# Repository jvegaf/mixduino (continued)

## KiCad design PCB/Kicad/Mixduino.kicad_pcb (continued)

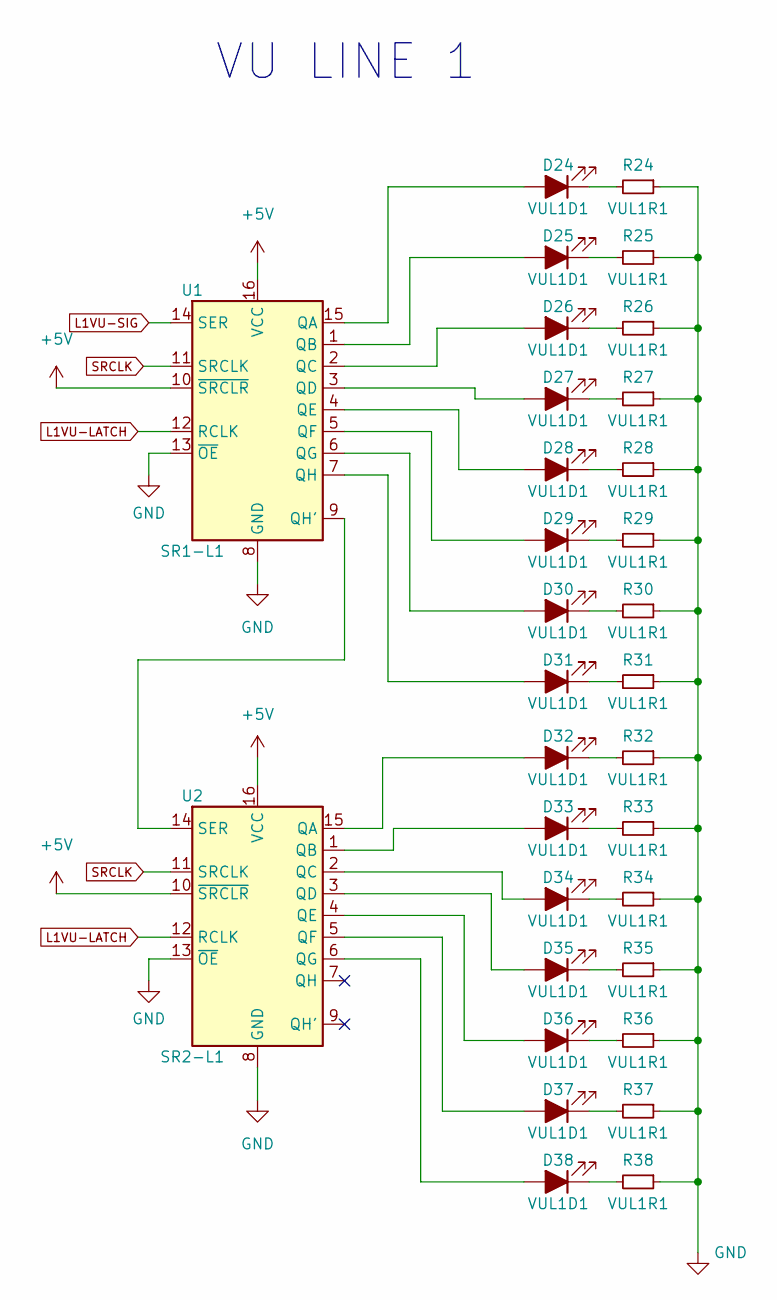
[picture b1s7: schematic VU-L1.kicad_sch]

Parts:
D24, D25, D26, D27, D28, D29, D30, D31, D32: VUL1D1; LED_GREEN
D33, D34, D35, D36: VUL1D1; LED_YELLOW
D37, D38: VUL1D1; LED_RED
R24, R25, R26, R27, R28, R29, R30, R31, R32, R33, R34, R35, R36, R37, R38: VUL1R1; R_1206_3216Metric_Pad1.30x1.75mm_HandSolder
U1: SR1-L1; SO-16_3.9x9.9mm_P1.27mm
U2: SR2-L1; SO-16_3.9x9.9mm_P1.27mm

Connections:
GND: R24.1, R25.1, R26.1, R27.1, R28.1, R29.1, R30.1, R31.1, R32.1, R33.1, R34.1, R35.1, R36.1, R37.1, R38.1, U1.8 (GND), U1.13 (~OE), U2.8 (GND), U2.13 (~OE); also elsewhere on the board
L1VU-LATCH: U1.12 (RCLK), U2.12 (RCLK); also elsewhere on the board
L1VU-SIG: U1.14 (SER); also elsewhere on the board
unnamed: D24.1 (K), R24.2
unnamed: D24.2 (A), U1.15 (QA)
unnamed: D25.1 (K), R25.2
unnamed: D25.2 (A), U1.1 (QB)
unnamed: D26.1 (K), R26.2
unnamed: D26.2 (A), U1.2 (QC)
unnamed: D27.1 (K), R27.2
unnamed: D27.2 (A), U1.3 (QD)
unnamed: D28.1 (K), R28.2
unnamed: D28.2 (A), U1.4 (QE)
unnamed: D29.1 (K), R29.2
unnamed: D29.2 (A), U1.5 (QF)
unnamed: D30.1 (K), R30.2
unnamed: D30.2 (A), U1.6 (QG)
unnamed: D31.1 (K), R31.2
unnamed: D31.2 (A), U1.7 (QH)
unnamed: D32.1 (K), R32.2
unnamed: D32.2 (A), U2.15 (QA)
unnamed: D33.1 (K), R33.2
unnamed: D33.2 (A), U2.1 (QB)
unnamed: D34.1 (K), R34.2
unnamed: D34.2 (A), U2.2 (QC)
unnamed: D35.1 (K), R35.2
unnamed: D35.2 (A), U2.3 (QD)
unnamed: D36.1 (K), R36.2
unnamed: D36.2 (A), U2.4 (QE)
unnamed: D37.1 (K), R37.2
unnamed: D37.2 (A), U2.5 (QF)
unnamed: D38.1 (K), R38.2
unnamed: D38.2 (A), U2.6 (QG)
unnamed: U1.9 (QH'), U2.14 (SER)
SRCLK: U1.11 (SRCLK), U2.11 (SRCLK); also elsewhere on the board
VCC: U1.10 (~SRCLR), U1.16 (VCC), U2.10 (~SRCLR), U2.16 (VCC); also elsewhere on the board

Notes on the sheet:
VU LINE 1

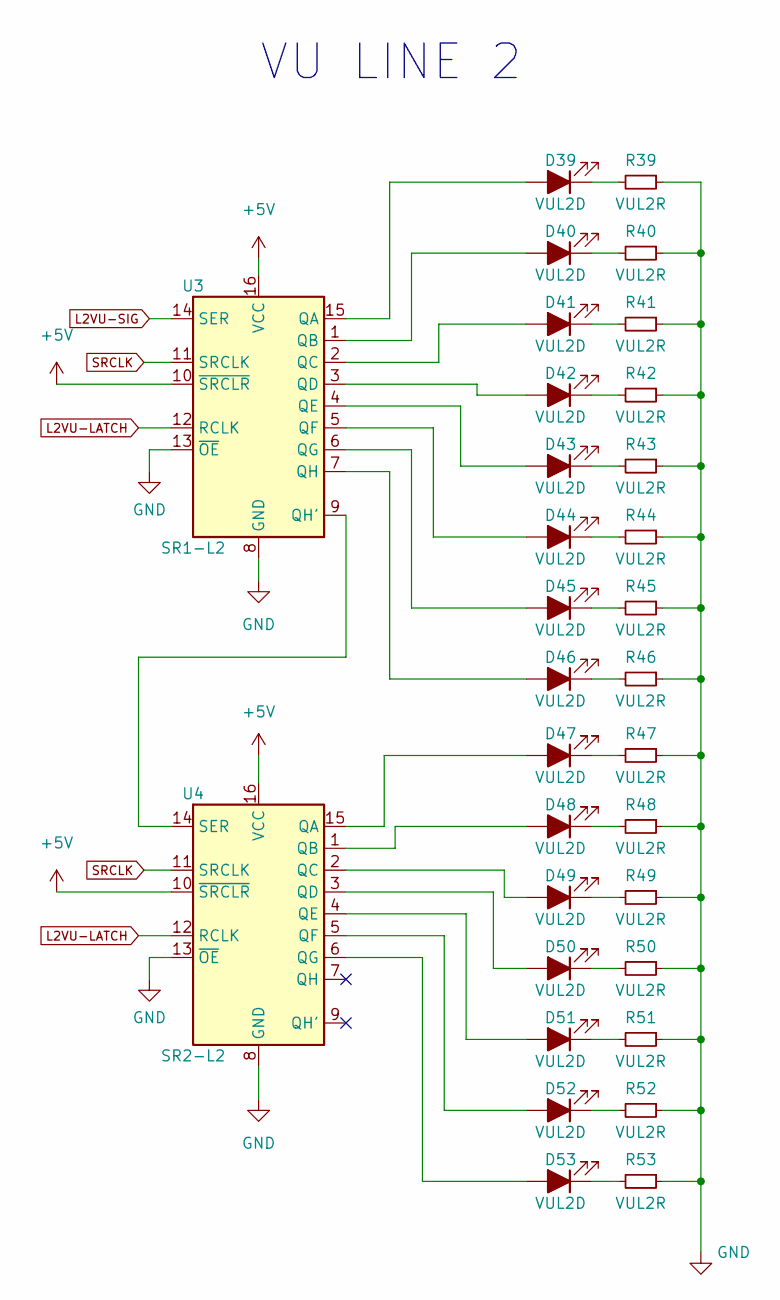
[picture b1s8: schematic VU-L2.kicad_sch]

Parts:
D39, D40, D41, D42, D43, D44, D45, D46, D47: VUL2D; LED_GREEN
D48, D49, D50, D51: VUL2D; LED_YELLOW
D52, D53: VUL2D; LED_RED
R39, R40, R41, R42, R43, R44, R45, R46, R47, R48, R49, R50, R51, R52, R53: VUL2R; R_1206_3216Metric_Pad1.30x1.75mm_HandSolder
U3: SR1-L2; SO-16_3.9x9.9mm_P1.27mm
U4: SR2-L2; SO-16_3.9x9.9mm_P1.27mm

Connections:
GND: R39.1, R40.1, R41.1, R42.1, R43.1, R44.1, R45.1, R46.1, R47.1, R48.1, R49.1, R50.1, R51.1, R52.1, R53.1, U3.8 (GND), U3.13 (~OE), U4.8 (GND), U4.13 (~OE); also elsewhere on the board
L2VU-LATCH: U3.12 (RCLK), U4.12 (RCLK); also elsewhere on the board
L2VU-SIG: U3.14 (SER); also elsewhere on the board
unnamed: D39.1 (K), R39.2
unnamed: D39.2 (A), U3.15 (QA)
unnamed: D40.1 (K), R40.2
unnamed: D40.2 (A), U3.1 (QB)
unnamed: D41.1 (K), R41.2
unnamed: D41.2 (A), U3.2 (QC)
unnamed: D42.1 (K), R42.2
unnamed: D42.2 (A), U3.3 (QD)
unnamed: D43.1 (K), R43.2
unnamed: D43.2 (A), U3.4 (QE)
unnamed: D44.1 (K), R44.2
unnamed: D44.2 (A), U3.5 (QF)
unnamed: D45.1 (K), R45.2
unnamed: D45.2 (A), U3.6 (QG)
unnamed: D46.1 (K), R46.2
unnamed: D46.2 (A), U3.7 (QH)
unnamed: D47.1 (K), R47.2
unnamed: D47.2 (A), U4.15 (QA)
unnamed: D48.1 (K), R48.2
unnamed: D48.2 (A), U4.1 (QB)
unnamed: D49.1 (K), R49.2
unnamed: D49.2 (A), U4.2 (QC)
unnamed: D50.1 (K), R50.2
unnamed: D50.2 (A), U4.3 (QD)
unnamed: D51.1 (K), R51.2
unnamed: D51.2 (A), U4.4 (QE)
unnamed: D52.1 (K), R52.2
unnamed: D52.2 (A), U4.5 (QF)
unnamed: D53.1 (K), R53.2
unnamed: D53.2 (A), U4.6 (QG)
unnamed: U3.9 (QH'), U4.14 (SER)
SRCLK: U3.11 (SRCLK), U4.11 (SRCLK); also elsewhere on the board
VCC: U3.10 (~SRCLR), U3.16 (VCC), U4.10 (~SRCLR), U4.16 (VCC); also elsewhere on the board

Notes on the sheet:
VU LINE 2

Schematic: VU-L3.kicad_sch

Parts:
D54, D55, D56, D57, D58, D59, D60, D61, D62: VUL3D; LED_GREEN
D63, D64, D65, D66: VUL3D; LED_YELLOW
D67, D68: VUL3D; LED_RED
R54, R55, R56, R57, R58, R59, R60, R61, R62, R63, R64, R65, R66, R67, R68: VUL3R; R_1206_3216Metric_Pad1.30x1.75mm_HandSolder
U5: SR1-L3; SO-16_3.9x9.9mm_P1.27mm
U6: SR2-L3; SO-16_3.9x9.9mm_P1.27mm

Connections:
GND: R54.1, R55.1, R56.1, R57.1, R58.1, R59.1, R60.1, R61.1, R62.1, R63.1, R64.1, R65.1, R66.1, R67.1, R68.1, U5.8 (GND), U5.13 (~OE), U6.8 (GND), U6.13 (~OE); also elsewhere on the board
L3VU-LATCH: U5.12 (RCLK), U6.12 (RCLK); also elsewhere on the board
L3VU-SIG: U5.14 (SER); also elsewhere on the board
unnamed: D54.1 (K), R54.2
unnamed: D54.2 (A), U5.15 (QA)
unnamed: D55.1 (K), R55.2
unnamed: D55.2 (A), U5.1 (QB)
unnamed: D56.1 (K), R56.2
unnamed: D56.2 (A), U5.2 (QC)
unnamed: D57.1 (K), R57.2
unnamed: D57.2 (A), U5.3 (QD)
unnamed: D58.1 (K), R58.2
unnamed: D58.2 (A), U5.4 (QE)
unnamed: D59.1 (K), R59.2
unnamed: D59.2 (A), U5.5 (QF)
unnamed: D60.1 (K), R60.2
unnamed: D60.2 (A), U5.6 (QG)
unnamed: D61.1 (K), R61.2
unnamed: D61.2 (A), U5.7 (QH)
unnamed: D62.1 (K), R62.2
unnamed: D62.2 (A), U6.15 (QA)
unnamed: D63.1 (K), R63.2
unnamed: D63.2 (A), U6.1 (QB)
unnamed: D64.1 (K), R64.2
unnamed: D64.2 (A), U6.2 (QC)
unnamed: D65.1 (K), R65.2
unnamed: D65.2 (A), U6.3 (QD)
unnamed: D66.1 (K), R66.2
unnamed: D66.2 (A), U6.4 (QE)
unnamed: D67.1 (K), R67.2
unnamed: D67.2 (A), U6.5 (QF)
unnamed: D68.1 (K), R68.2
unnamed: D68.2 (A), U6.6 (QG)
unnamed: U5.9 (QH'), U6.14 (SER)
SRCLK: U5.11 (SRCLK), U6.11 (SRCLK); also elsewhere on the board
VCC: U5.10 (~SRCLR), U5.16 (VCC), U6.10 (~SRCLR), U6.16 (VCC); also elsewhere on the board

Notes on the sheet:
VU LINE 3

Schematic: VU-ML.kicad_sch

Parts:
D69, D70, D71, D72, D73, D74, D75, D76, D77: VUMLD; LED_GREEN
D78, D79, D80, D81: VUMLD; LED_YELLOW
D82, D83: VUMLD; LED_RED
R69, R70, R71, R72, R73, R74, R75, R76, R77, R78, R79, R80, R81, R82, R83: VUMLR; R_1206_3216Metric_Pad1.30x1.75mm_HandSolder
U7: SR1-ML; SO-16_3.9x9.9mm_P1.27mm
U8: SR2-ML; SO-16_3.9x9.9mm_P1.27mm

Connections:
GND: R69.1, R70.1, R71.1, R72.1, R73.1, R74.1, R75.1, R76.1, R77.1, R78.1, R79.1, R80.1, R81.1, R82.1, R83.1, U7.8 (GND), U7.13 (~OE), U8.8 (GND), U8.13 (~OE); also elsewhere on the board
MLVU-LATCH: U7.12 (RCLK), U8.12 (RCLK); also elsewhere on the board
MLVU-SIG: U7.14 (SER); also elsewhere on the board
unnamed: D69.1 (K), R69.2
unnamed: D69.2 (A), U7.15 (QA)
unnamed: D70.1 (K), R70.2
unnamed: D70.2 (A), U7.1 (QB)
unnamed: D71.1 (K), R71.2
unnamed: D71.2 (A), U7.2 (QC)
unnamed: D72.1 (K), R72.2
unnamed: D72.2 (A), U7.3 (QD)
unnamed: D73.1 (K), R73.2
unnamed: D73.2 (A), U7.4 (QE)
unnamed: D74.1 (K), R74.2
unnamed: D74.2 (A), U7.5 (QF)
unnamed: D75.1 (K), R75.2
unnamed: D75.2 (A), U7.6 (QG)
unnamed: D76.1 (K), R76.2
unnamed: D76.2 (A), U7.7 (QH)
unnamed: D77.1 (K), R77.2
unnamed: D77.2 (A), U8.15 (QA)
unnamed: D78.1 (K), R78.2
unnamed: D78.2 (A), U8.1 (QB)
unnamed: D79.1 (K), R79.2
unnamed: D79.2 (A), U8.2 (QC)
unnamed: D80.1 (K), R80.2
unnamed: D80.2 (A), U8.3 (QD)
unnamed: D81.1 (K), R81.2
unnamed: D81.2 (A), U8.4 (QE)
unnamed: D82.1 (K), R82.2
unnamed: D82.2 (A), U8.5 (QF)
unnamed: D83.1 (K), R83.2
unnamed: D83.2 (A), U8.6 (QG)
unnamed: U7.9 (QH'), U8.14 (SER)
SRCLK: U7.11 (SRCLK), U8.11 (SRCLK); also elsewhere on the board
VCC: U7.10 (~SRCLR), U7.16 (VCC), U8.10 (~SRCLR), U8.16 (VCC); also elsewhere on the board

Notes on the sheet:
VU MASTER LEFT

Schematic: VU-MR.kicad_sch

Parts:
D84, D85, D86, D87, D88, D89, D90, D91, D92: VUMRD; LED_GREEN
D93, D94, D95, D96: VUMRD; LED_YELLOW
D97, D98: VUMRD; LED_RED
R84, R85, R86, R87, R88, R89, R90, R91, R92, R93, R94, R95, R96, R97, R98: VUMRR; R_1206_3216Metric_Pad1.30x1.75mm_HandSolder
U9: SR1-MR; SO-16_3.9x9.9mm_P1.27mm
U10: SR2-MR; SO-16_3.9x9.9mm_P1.27mm

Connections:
GND: R84.1, R85.1, R86.1, R87.1, R88.1, R89.1, R90.1, R91.1, R92.1, R93.1, R94.1, R95.1, R96.1, R97.1, R98.1, U9.8 (GND), U9.13 (~OE), U10.8 (GND), U10.13 (~OE); also elsewhere on the board
MRVU-LATCH: U9.12 (RCLK), U10.12 (RCLK); also elsewhere on the board
MRVU-SIG: U9.14 (SER); also elsewhere on the board
unnamed: D84.1 (K), R84.2
unnamed: D84.2 (A), U9.15 (QA)
unnamed: D85.1 (K), R85.2
unnamed: D85.2 (A), U9.1 (QB)
unnamed: D86.1 (K), R86.2
unnamed: D86.2 (A), U9.2 (QC)
unnamed: D87.1 (K), R87.2
unnamed: D87.2 (A), U9.3 (QD)
unnamed: D88.1 (K), R88.2
unnamed: D88.2 (A), U9.4 (QE)
unnamed: D89.1 (K), R89.2
unnamed: D89.2 (A), U9.5 (QF)
unnamed: D90.1 (K), R90.2
unnamed: D90.2 (A), U9.6 (QG)
unnamed: D91.1 (K), R91.2
unnamed: D91.2 (A), U9.7 (QH)
unnamed: D92.1 (K), R92.2
unnamed: D92.2 (A), U10.15 (QA)
unnamed: D93.1 (K), R93.2
unnamed: D93.2 (A), U10.1 (QB)
unnamed: D94.1 (K), R94.2
unnamed: D94.2 (A), U10.2 (QC)
unnamed: D95.1 (K), R95.2
unnamed: D95.2 (A), U10.3 (QD)
unnamed: D96.1 (K), R96.2
unnamed: D96.2 (A), U10.4 (QE)
unnamed: D97.1 (K), R97.2
unnamed: D97.2 (A), U10.5 (QF)
unnamed: D98.1 (K), R98.2
unnamed: D98.2 (A), U10.6 (QG)
unnamed: U9.9 (QH'), U10.14 (SER)
SRCLK: U9.11 (SRCLK), U10.11 (SRCLK); also elsewhere on the board
VCC: U9.10 (~SRCLR), U9.16 (VCC), U10.10 (~SRCLR), U10.16 (VCC); also elsewhere on the board

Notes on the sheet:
VU MASTER RIGHT

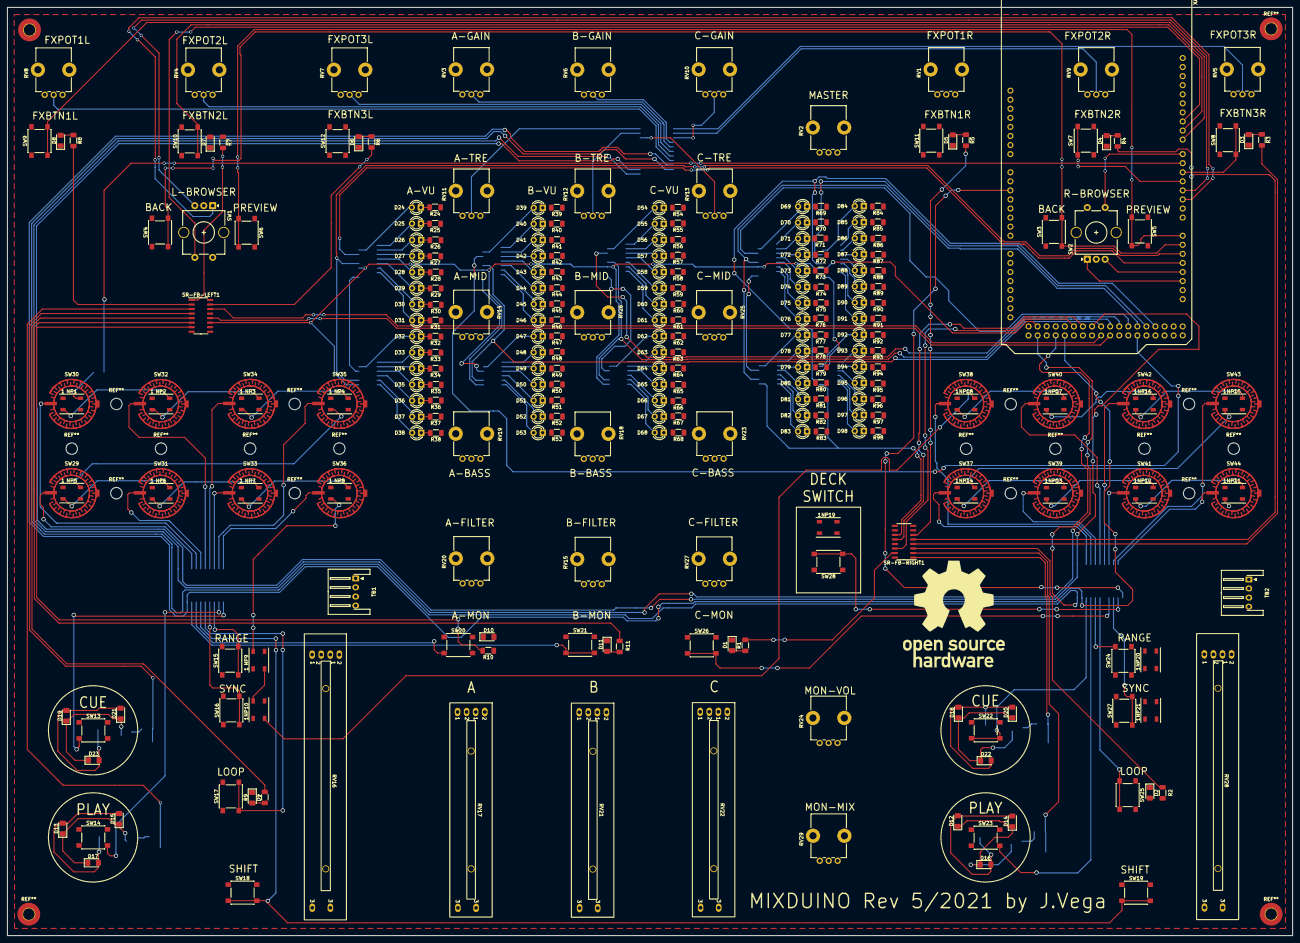
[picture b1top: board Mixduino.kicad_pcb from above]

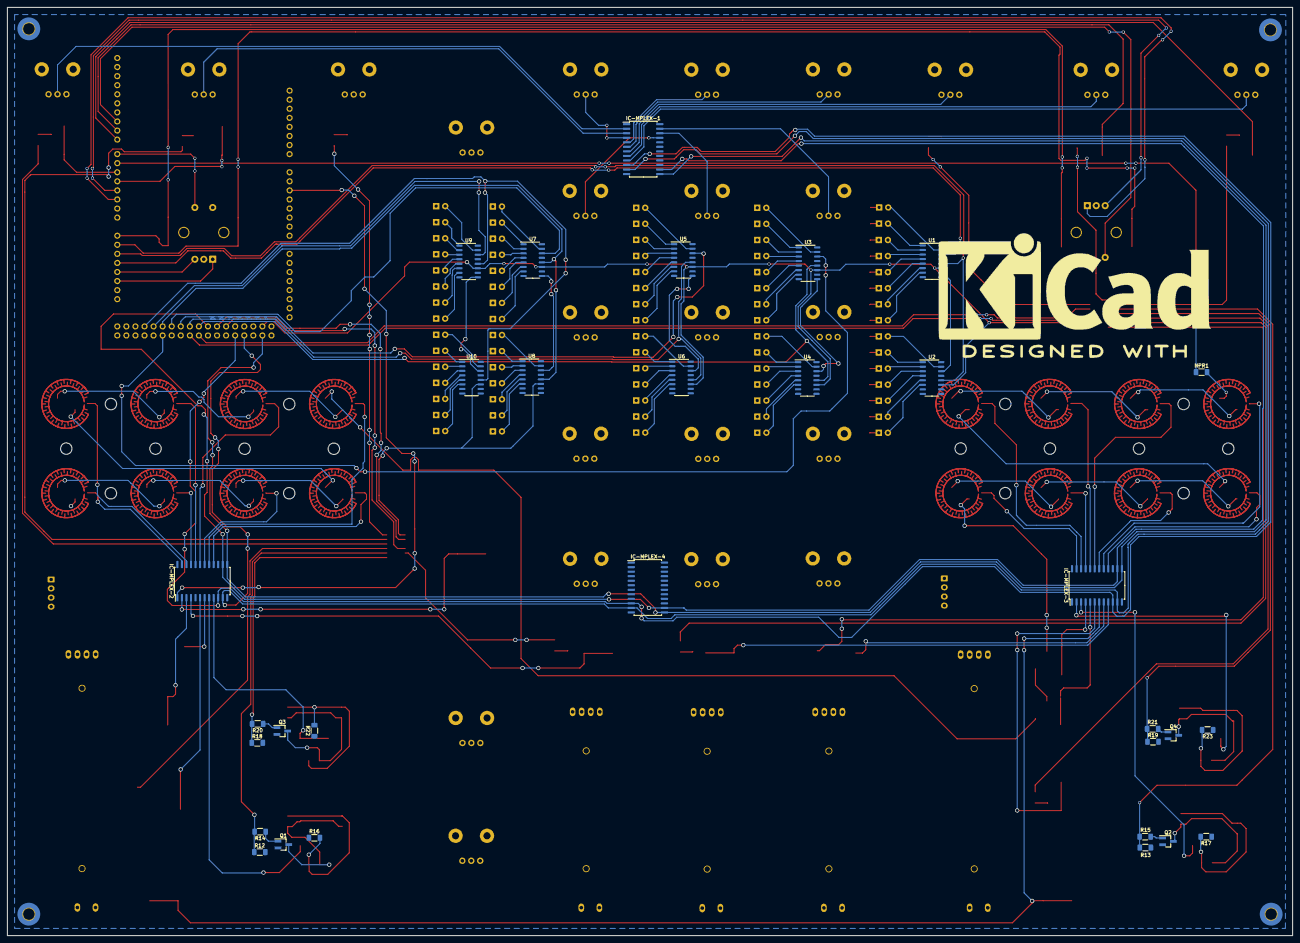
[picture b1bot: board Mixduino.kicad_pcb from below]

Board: 2 copper layers, 360.0 x 260.0 mm, 314 parts (31 on the bottom side), 316 nets.

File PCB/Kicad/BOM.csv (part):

Ref,Qnty,Value,Cmp name,Footprint,Description,Vendor
"BCUELD1, ",1,LED_ALT,LED_Filled,LED_THT:LED_Rectangular_W3.0mm_H2.0mm,"Light emitting diode, filled shape",
"BCUELR1, ",1,R_Small,R_Small,Resistor_SMD:R_1206_3216Metric_Pad1.30x1.75mm_HandSolder,"Resistor, small symbol",
"BCUERD1, ",1,LED_ALT,LED_Filled,LED_THT:LED_Rectangular_W3.0mm_H2.0mm,"Light emitting diode, filled shape",
"BCUERR1, ",1,R_Small,R_Small,Resistor_SMD:R_1206_3216Metric_Pad1.30x1.75mm_HandSolder,"Resistor, small symbol",
"BHPL1D1, ",1,LED_ALT,LED_Filled,LED_THT:LED_Rectangular_W3.0mm_H2.0mm,"Light emitting diode, filled shape",
"BHPL1R1, ",1,R_Small,R_Small,Resistor_SMD:R_1206_3216Metric_Pad1.30x1.75mm_HandSolder,"Resistor, small symbol",
"BHPL2D1, ",1,LED_ALT,LED_Filled,LED_THT:LED_Rectangular_W3.0mm_H2.0mm,"Light emitting diode, filled shape",
"BHPL2R1, ",1,R_Small,R_Small,Resistor_SMD:R_1206_3216Metric_Pad1.30x1.75mm_HandSolder,"Resistor, small symbol",
"BPLAYLD1, ",1,LED_ALT,LED_Filled,LED_THT:LED_Rectangular_W3.0mm_H2.0mm,"Light emitting diode, filled shape",
"BPLAYLR1, ",1,R_Small,R_Small,Resistor_SMD:R_1206_3216Metric_Pad1.30x1.75mm_HandSolder,"Resistor, small symbol",
"BPLAYRD1, ",1,LED_ALT,LED_Filled,LED_THT:LED_Rectangular_W3.0mm_H2.0mm,"Light emitting diode, filled shape",
"BPLAYRR1, ",1,R_Small,R_Small,Resistor_SMD:R_1206_3216Metric_Pad1.30x1.75mm_HandSolder,"Resistor, small symbol",
"D23, ",1,LED_ALT,LED_Filled,LED_THT:LED_Rectangular_W3.0mm_H2.0mm,"Light emitting diode, filled shape",
"IC-POTS-1, ",1,"74HC4067D,653","74HC4067D,653",Package_SO:SOIC-24W_7.5x15.4mm_P1.27mm,74HC(T)4067 - 16-channel analog multiplexer/demultiplexer@en-us,
"PADL-D1, PADL-D2, PADL-D3, PADL-D4, PADL-D5, PADL-D6, PADL-D7, PADL-D8, ",8,WS2812B,WS2812B,LED_SMD:LED_WS2812B_PLCC4_5.0x5.0mm_P3.2mm,RGB LED with integrated controller,
"PADL-IN-R1, ",1,R_Small,R_Small,Resistor_SMD:R_1206_3216Metric_Pad1.30x1.75mm_HandSolder,"Resistor, small symbol",
"PADR-D1, PADR-D2, PADR-D3, PADR-D4, PADR-D5, PADR-D6, PADR-D7, PADR-D8, ",8,WS2812B,WS2812B,LED_SMD:LED_WS2812B_PLCC4_5.0x5.0mm_P3.2mm,RGB LED with integrated controller,
"PADR-IN-R1, ",1,R_Small,R_Small,Resistor_SMD:R_1206_3216Metric_Pad1.30x1.75mm_HandSolder,"Resistor, small symbol",
"R23, ",1,R_Small,R_Small,Resistor_SMD:R_1206_3216Metric_Pad1.30x1.75mm_HandSolder,"Resistor, small symbol",
"RV1, ",1,FADERL1,R_Potentiometer,Library:fader-L60,Potentiometer,
"RV2, ",1,FADERL2,R_Potentiometer,Library:fader-L60,Potentiometer,
"RV3, ",1,FADERL3,R_Potentiometer,Library:fader-L60,Potentiometer,
"RV4, ",1,PITCH-L,R_Potentiometer,Library:fader-L75,Potentiometer,
"RV5, ",1,PITH-R,R_Potentiometer,Library:fader-L75,Potentiometer,
"RV6, ",1,PMIX-HP,R_Potentiometer,Potentiometer_THT:Potentiometer_Bourns_PTV09A-1_Single_Vertical,Potentiometer,
"RV7, ",1,FILTERL1,R_Potentiometer,Potentiometer_THT:Potentiometer_Bourns_PTV09A-1_Single_Vertical,Potentiometer,
"RV8, ",1,FILTERL2,R_Potentiometer,Potentiometer_THT:Potentiometer_Bourns_PTV09A-1_Single_Vertical,Potentiometer,
"RV9, ",1,FILTERL3,R_Potentiometer,Potentiometer_THT:Potentiometer_Bourns_PTV09A-1_Single_Vertical,Potentiometer,
"RV10, ",1,PFX1L,R_Potentiometer,Potentiometer_THT:Potentiometer_Bourns_PTV09A-1_Single_Vertical,Potentiometer,
"RV11, ",1,PFX1R,R_Potentiometer,Potentiometer_THT:Potentiometer_Bourns_PTV09A-1_Single_Vertical,Potentiometer,
"RV12, ",1,PVOL-HP,R_Potentiometer,Potentiometer_THT:Potentiometer_Bourns_PTV09A-1_Single_Vertical,Potentiometer,
"RV13, ",1,BASL1,R_Potentiometer,Potentiometer_THT:Potentiometer_Bourns_PTV09A-1_Single_Vertical,Potentiometer,
"RV14, ",1,BASL2,R_Potentiometer,Potentiometer_THT:Potentiometer_Bourns_PTV09A-1_Single_Vertical,Potentiometer,
"RV15, ",1,BASL3,R_Potentiometer,Potentiometer_THT:Potentiometer_Bourns_PTV09A-1_Single_Vertical,Potentiometer,
"RV16, ",1,PFX2L,R_Potentiometer,Potentiometer_THT:Potentiometer_Bourns_PTV09A-1_Single_Vertical,Potentiometer,
"RV17, ",1,PFX2R,R_Potentiometer,Potentiometer_THT:Potentiometer_Bourns_PTV09A-1_Single_Vertical,Potentiometer,
"RV18, ",1,PMASTER,R_Potentiometer,Potentiometer_THT:Potentiometer_Bourns_PTV09A-1_Single_Vertical,Potentiometer,
"RV19, ",1,MIDL1,R_Potentiometer,Potentiometer_THT:Potentiometer_Bourns_PTV09A-1_Single_Vertical,Potentiometer,
"RV20, ",1,MIDL2,R_Potentiometer,Potentiometer_THT:Potentiometer_Bourns_PTV09A-1_Single_Vertical,Potentiometer,
"RV21, ",1,MIDL3,R_Potentiometer,Potentiometer_THT:Potentiometer_Bourns_PTV09A-1_Single_Vertical,Potentiometer,
"RV22, ",1,PFX3L,R_Potentiometer,Potentiometer_THT:Potentiometer_Bourns_PTV09A-1_Single_Vertical,Potentiometer,
"RV23, ",1,PFX3R,R_Potentiometer,Potentiometer_THT:Potentiometer_Bourns_PTV09A-1_Single_Vertical,Potentiometer,
"RV24, ",1,TREL1,R_Potentiometer,Potentiometer_THT:Potentiometer_Bourns_PTV09A-1_Single_Vertical,Potentiometer,
"RV25, ",1,TREL2,R_Potentiometer,Potentiometer_THT:Potentiometer_Bourns_PTV09A-1_Single_Vertical,Potentiometer,
"RV26, ",1,TREL3,R_Potentiometer,Potentiometer_THT:Potentiometer_Bourns_PTV09A-1_Single_Vertical,Potentiometer,
"RV27, ",1,GAINL1,R_Potentiometer,Potentiometer_THT:Potentiometer_Bourns_PTV09A-1_Single_Vertical,Potentiometer,
"RV28, ",1,GAINL2,R_Potentiometer,Potentiometer_THT:Potentiometer_Bourns_PTV09A-1_Single_Vertical,Potentiometer,
"RV29, ",1,GAINL3,R_Potentiometer,Potentiometer_THT:Potentiometer_Bourns_PTV09A-1_Single_Vertical,Potentiometer,
"SW1, ",1,SWPADL1,SW_Push,Library:sw-pad,"Push button switch, generic, two pins",
"SW2, ",1,SWPADL2,SW_Push,Library:sw-pad,"Push button switch, generic, two pins",
"SW3, ",1,SWPADL3,SW_Push,Library:sw-pad,"Push button switch, generic, two pins",
"SW4, ",1,SWPADL4,SW_Push,Library:sw-pad,"Push button switch, generic, two pins",
"SW5, ",1,SWPADL5,SW_Push,Library:sw-pad,"Push button switch, generic, two pins",
"SW6, ",1,SWPADL6,SW_Push,Library:sw-pad,"Push button switch, generic, two pins",
"SW7, ",1,SWPADL7,SW_Push,Library:sw-pad,"Push button switch, generic, two pins",
"SW8, ",1,SWPADL8,SW_Push,Library:sw-pad,"Push button switch, generic, two pins",
"SW9, ",1,SWPADR1,SW_Push,Library:sw-pad,"Push button switch, generic, two pins",
"SW10, ",1,SWPADR2,SW_Push,Library:sw-pad,"Push button switch, generic, two pins",
"SW11, ",1,SWPADR3,SW_Push,Library:sw-pad,"Push button switch, generic, two pins",
"SW12, ",1,SWPADR4,SW_Push,Library:sw-pad,"Push button switch, generic, two pins",
"SW13, ",1,SWPADR5,SW_Push,Library:sw-pad,"Push button switch, generic, two pins",
"SW14, ",1,SWPADR6,SW_Push,Library:sw-pad,"Push button switch, generic, two pins",
"SW15, ",1,SWPADR7,SW_Push,Library:sw-pad,"Push button switch, generic, two pins",
"SW16, ",1,SWPADR8,SW_Push,Library:sw-pad,"Push button switch, generic, two pins",
"SW17, ",1,SWPLAYL,SW_Push,Button_Switch_THT:SW_PUSH_6mm_H5mm,"Push button switch, generic, two pins",
"SW18, ",1,SWCUEL,SW_Push,Button_Switch_THT:SW_PUSH_6mm_H5mm,"Push button switch, generic, two pins",
"SW19, ",1,SWSHIFTL,SW_Push,Button_Switch_THT:SW_PUSH_6mm_H5mm,"Push button switch, generic, two pins",
"SW20, ",1,SWSYNCL,SW_Push,Button_Switch_THT:SW_PUSH_6mm_H5mm,"Push button switch, generic, two pins",
"SW21, ",1,SWRANGEL,SW_Push,Button_Switch_THT:SW_PUSH_6mm_H5mm,"Push button switch, generic, two pins",
"SW22, ",1,SWFX1L,SW_Push,Button_Switch_THT:SW_PUSH_6mm_H5mm,"Push button switch, generic, two pins",
"SW23, ",1,SWFX2L,SW_Push,Button_Switch_THT:SW_PUSH_6mm_H5mm,"Push button switch, generic, two pins",
"SW24, ",1,SWFX3L,SW_Push,Button_Switch_THT:SW_PUSH_6mm_H5mm,"Push button switch, generic, two pins",
"SW25, ",1,SWBR-PREVL,SW_Push,Button_Switch_THT:SW_PUSH_6mm_H5mm,"Push button switch, generic, two pins",
"SW26, ",1,SWBR-BACKL,SW_Push,Button_Switch_THT:SW_PUSH_6mm_H5mm,"Push button switch, generic, two pins",
"SW27, ",1,SWPLAYR,SW_Push,Button_Switch_THT:SW_PUSH_6mm_H5mm,"Push button switch, generic, two pins",
"SW28, ",1,SWCUER,SW_Push,Button_Switch_THT:SW_PUSH_6mm_H5mm,"Push button switch, generic, two pins",
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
